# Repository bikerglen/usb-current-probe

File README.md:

# usb-current-probe
Simple USB 2.0 Type A Connector Current Probe

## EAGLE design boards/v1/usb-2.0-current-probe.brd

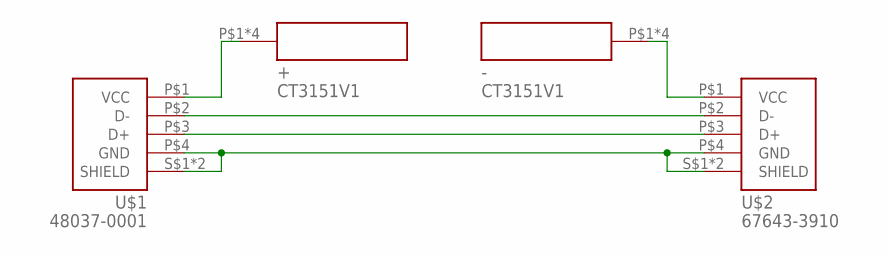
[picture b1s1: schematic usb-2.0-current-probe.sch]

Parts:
+: CT3151V1
-: CT3151V1
U$1: 48037-0001
U$2: 67643-3910

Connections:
GND: U$1.P$4 (GND), U$1.S$1 (SHIELD), U$1.S$2 (SHIELD), U$2.P$4 (GND), U$2.S$1 (SHIELD), U$2.S$2 (SHIELD)
unnamed: U$1.P$2 (D-), U$2.P$2 (D-)
unnamed: U$1.P$3 (D+), U$2.P$3 (D+)
VLOAD: -.P$1, -.P$2, -.P$3, -.P$4, U$2.P$1 (VCC)
VUSB: +.P$1, +.P$2, +.P$3, +.P$4, U$1.P$1 (VCC)

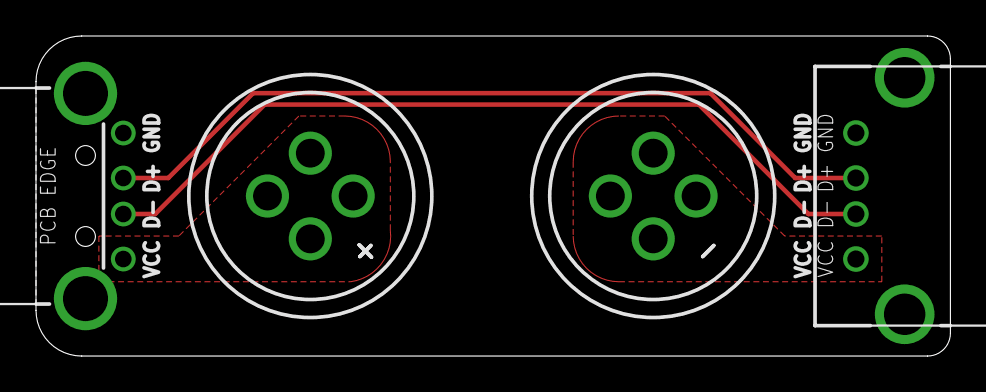
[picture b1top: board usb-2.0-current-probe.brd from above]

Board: 2 copper layers, 50.8 x 17.8 mm, 4 parts (0 on the bottom side), 5 nets.

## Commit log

2019-12-15 initial checkin
